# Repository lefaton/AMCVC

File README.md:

# AMCVC — Arduino MIDI to CV Converter

A MIDI-to-CV daughter board designed to drive the [x0x-heart](http://www.openmusiclabs.com/projects/x0x-heart/) — an open-source clone of the Roland TB-303 bass synthesizer engine. The board sits between a MIDI source and the x0x-heart, converting MIDI note and CC messages into analog control voltages (CV) and digital gate/control signals.

Built around a **Teensy++ 1.0** microcontroller and a **MCP4922 12-bit dual DAC** via SPI. The firmware is written as an Arduino sketch.

> **Status:** The firmware is working and was successfully tested on a prototype. The
> schematic and board netlist have been corrected (2026 revision) — the two changed nets
> (`~SHDN`, `~LDAC`) still need re-routing in Eagle plus a DRC pass before fabrication.

---

## Context — What Is the x0x-heart?

The [x0x-heart](http://www.openmusiclabs.com/projects/x0x-heart/) is an open hardware recreation of the Roland TB-303 synthesizer core. It exposes CV and gate inputs for pitch, filter cutoff, and a set of digital control lines (decay, accent, slide in, slide out) that replicate the 303's characteristic playing articulations.

The AMCVC board plugs into those inputs and translates MIDI messages into the signals the x0x-heart expects, making it possible to sequence and play the 303 engine from any standard MIDI controller or DAW.

---

## Hardware Overview

### Microcontroller — Teensy++ 1.0

The [Teensy++ 1.0](https://www.pjrc.com/teensy/) is a compact USB-capable AVR microcontroller board (AT90USB1286). It runs the Arduino-compatible MIDI library and handles SPI communication with the DAC. A reference pinout is included in `Documents/Teensy 1.0++ pinout.png`.

### DAC — MCP4922 (12-bit, dual-channel, SPI)

The [MCP4922](https://www.microchip.com/MCP4922) is a 12-bit dual-output DAC communicating over SPI. It provides two independent CV outputs:

| Channel | Purpose     | Constant         | Driven by         |
|---------|-------------|------------------|-------------------|
| A (0)   | VCO pitch   | `VCO_DAC_ID = 0` | MIDI note number  |
| B (1)   | VCF cutoff  | `VCF_DAC_ID = 1` | MIDI CC 74        |

SPI is configured MSB-first, SPI Mode 0. The 16-bit command word sent to the MCP4922 is:

```
Bit 15   : A/B   — channel select (0 = channel A / VCO, 1 = channel B / VCF)
Bit 14   : BUF   — input buffer (0 = unbuffered)
Bit 13   : /GA   — gain select (1 = 1× gain, 0–Vref)
Bit 12   : /SHDN — output enable (1 = active)
Bits 11–0: 12-bit DAC value
```

`WriteDAC(channel, value)` builds the word per channel: it ORs in `0x3000` (bits 13
and 12 → 1× gain, output active) and sets bit 15 from the channel argument, so both
the VCO (channel A) and VCF (channel B) outputs are addressable.

### MIDI Isolation — 6N138 Optocoupler

MIDI input is electrically isolated using a [6N138](Documents/Datasheets/6N138.pdf) high-speed optocoupler, following the standard MIDI electrical interface specification. This prevents ground loops between the MIDI source and the synth circuitry.

---

## Pin Assignments (Teensy++ 1.0)

| Pin | Direction | Function                     |
|-----|-----------|------------------------------|
| 2   | INPUT     | MIDI input (via 6N138)       |
| 4   | OUTPUT    | Decay control (x0x-heart)    |
| 5   | OUTPUT    | Front panel LED              |
| 6   | OUTPUT    | Board LED                    |
| 7   | OUTPUT    | Accent control (x0x-heart)   |
| 8   | OUTPUT    | Slide In control             |
| 9   | OUTPUT    | VCO Gate                     |
| 10  | OUTPUT    | SPI CS (MCP4922 chip select) |
| 11  | OUTPUT    | SPI LDAC (DAC latch)         |
| 12  | OUTPUT    | Slide Out control            |
| 13  | INPUT     | Square wave input (x0x)      |
| 14  | INPUT     | Saw wave input (x0x)         |
| 15  | OUTPUT    | Square wave output           |
| 16  | OUTPUT    | Saw wave output              |
| 17  | OUTPUT    | VCF Gate                     |

---

## MIDI Configuration

```cpp
const int MIDIChannel = 3;  // MIDI channel to listen on
```

The sketch listens on MIDI channel 3 only — `MIDI.begin(MIDIChannel)` filters out
all other channels at the library level. To change channel, edit this constant and
re-upload.

---

## MIDI Note to CV Conversion

### Pitch (VCO)

The firmware converts MIDI note numbers to a 12-bit DAC value using a linear mapping:

```cpp
const float VCO_CV_step     = 68.25;  // DAC counts per semitone
const int   MIDI_Min_Note   = 24;     // C1 (lowest accepted note)
const int   MIDI_Max_Note   = 84;     // C6 (highest accepted note)
const int   MIDI_Start_Offset = 24;   // note 24 maps to DAC value 0
const int   VCO_CV_Offset   = 0;      // global tuning offset in semitones
```

Conversion formula:

```
convertedVal = (note + VCO_CV_Offset - MIDI_Start_Offset) × VCO_CV_step
```

**Example values:**

| MIDI Note | Note Name     | DAC value | Approx. CV |
|-----------|---------------|-----------|------------|
| 24        | C1            | 0         | 0 V        |
| 36        | C2            | 819       | ~1 V       |
| 48        | C3            | 1638      | ~2 V       |
| 60        | C4 (middle C) | 2457      | ~3 V       |
| 72        | C5            | 3276      | ~4 V       |
| 84        | C6            | 4095      | ~5 V       |

The 60-semitone range (C1–C6) maps to 0–4095, giving **1V/octave** when the DAC reference voltage is 5V. Fine-tune `VCO_CV_step` if your VCO has a different V/oct scaling. The full lookup table is in `Documents/table_midi_cv.xlsx`.

### Gate

| MIDI event              | Gate pins      | Logic         |
|-------------------------|----------------|---------------|
| Note On (velocity > 0)  | pin 9 + pin 17 | LOW (active)  |
| Note Off / velocity = 0 | pin 9 + pin 17 | HIGH (off)    |

The x0x-heart gates are active-low. Both the VCO gate (pin 9) and VCF gate (pin 17)
are driven together.

### Note priority (monophonic note stack)

The firmware is monophonic but tracks held notes in a small stack (up to 8 notes):

- **Note On** pushes the note and plays it immediately (last-note priority).
- **Note Off** removes the note from the stack. Releasing a note that is *not* the
  one currently sounding does **not** cut the gate — it just leaves the stack.
- Releasing the sounding note falls back to the most recently held note still down;
  the gate only closes when no notes remain.

This makes legato/overlapping play behave the way a hardware mono synth does.

### VCF cutoff (CC 74)

MIDI **CC 74** (the standard "brightness"/cutoff controller) drives the VCF on DAC
channel B. Values 0–127 are mapped linearly to the full 12-bit range (0–4095).

---

## TB-303 Specific CC Messages

The x0x-heart exposes four articulation controls specific to the TB-303 playing style. The firmware maps MIDI CC messages to digital lines:

| CC  | Hex   | Function   | Effect when value > 100          |
|-----|-------|------------|----------------------------------|
| 99  | 0x63  | Decay      | Pin 4 LOW (decay enabled)        |
| 100 | 0x64  | Accent     | Pin 7 LOW (accent enabled)       |
| 101 | 0x65  | Slide In   | Pin 8 LOW (slide in enabled)     |
| 102 | 0x66  | Slide Out  | Pin 12 LOW (slide out enabled)   |

A CC value strictly above 100 (`triggerLimit = 0x64`) activates the control; 100 or
below deactivates it. CC 74 (cutoff) is the exception — it is a continuous value, not
a trigger (see [VCF cutoff](#vcf-cutoff-cc-74) above).

**Slide mutual exclusion:** Slide In and Slide Out are mutually exclusive — activating one automatically cancels the other, mirroring the 303's hardware behavior.

---

## Wave Pass-Through

The x0x-heart outputs both a **square wave** and a **sawtooth wave**. The AMCVC board reads these on pins 13/14 and re-outputs them on pins 15/16 every loop cycle, acting as a signal buffer:

```cpp
digitalWrite(sawWaveOut_Pin,    digitalRead(sawWaveIn_Pin));
digitalWrite(squareWaveOut_Pin, digitalRead(squareWaveIn_Pin));
```

---

## Repository Structure

```
sketch_MIDI_to_CV/
  sketch_MIDI_to_CV.ino       ← Arduino firmware (upload this to Teensy)

Documents/
  table_midi_cv.xlsx          ← Full MIDI note to CV conversion table
  Teensy 1.0++ pinout.png     ← Teensy++ 1.0 pin reference diagram
  x0x Heart - tb-303.fpd     ← Front panel design (Frontpanel Designer)
  x0xheartmanual.pdf          ← x0x-heart complete manual

  Eagle/
    *.sch   ← Circuit schematic (Eagle CAD) — use this as reference
    *.brd   ← PCB layout (Eagle CAD) ⚠️ 2 nets unrouted after netlist fix

  Datasheets/
    MCP4922.pdf               ← 12-bit dual DAC datasheet
    6N138.pdf                 ← MIDI optocoupler datasheet
```

> ⚠️ **PCB note:** The Eagle netlist bugs (`~SHDN` grounded, `~LDAC` floating) are fixed in
> both `.sch` and `.brd`. On the board these two nets are now **unrouted airwires** — open in
> Eagle, run ERC/forward-annotation, route `~SHDN` (→ +5V) and `~LDAC` (→ MCU pin 11), then DRC
> before sending to a fab.

---

## Setup

### Arduino Libraries Required

- **MIDI Library** — [FortySevenEffects/arduino_midi_library](https://github.com/FortySevenEffects/arduino_midi_library)
- **SPI** — built into the Arduino/Teensy core

### Upload Steps

1. Install [Teensyduino](https://www.pjrc.com/teensy/teensyduino.html)
2. Select board: **Teensy++ 1.0**
3. Set USB Type to **Serial** (for debug output)
4. Open `sketch_MIDI_to_CV/sketch_MIDI_to_CV.ino`
5. Upload

MIDI runs at 31250 baud on the hardware UART. Debug output runs at 57600 baud on USB Serial.

---

## Known Issues & Future Work

- **Two nets need routing** — after the 2026 netlist fixes, `~SHDN` and `~LDAC` are
  unrouted airwires on the board (see below); they must be routed in Eagle before a fab run
- **Monophonic only** — no chord support; the note stack gives last-note priority but a single voice
- **Firmware untested since revision** — the 2026 firmware changes (dual-channel DAC,
  VCF CC 74, note stack, channel filtering, non-blocking LED) have not yet been flashed
  and verified on hardware

### Fixed in the 2026 revision

**Schematic / PCB netlist** (corrected in both `.sch` and `.brd`, verified by netlist
re-parse — Eagle ERC/DRC still required):

- **DAC `~SHDN` no longer grounded** — pin 9 moved from `AGND` to `+5V`. It was tied to
  ground, which held both DAC outputs in permanent hardware shutdown (root cause of "no CV out")
- **DAC `~LDAC` now connected** — pin 8 wired to MCU pin 11; both were floating, so the
  latch line never transferred values to the outputs
- **VCF output labelled** — the `VOUTB` connector pad was renamed `UNUSED` → `VCF_CUTOFF`

> On the board, the two changed nets (`~SHDN`, `~LDAC`) are left as **airwires** — the old
> AGND copper at pad 9 was removed so nothing shorts. Open the `.brd` in Eagle, run
> ERC/forward-annotation, route the two airwires, then DRC.

**Firmware:**

- **VCF CV** — DAC channel B is now driven from MIDI CC 74
- **MIDI channel filtering** — `MIDI.begin(MIDIChannel)` replaces `MIDI_CHANNEL_OMNI`
- **Gate latency** — the LED blink is non-blocking, so Note On no longer delays the DAC write by 25 ms
- **Stuck-note edge cases** — a note stack prevents Note Off of an inactive note from cutting the gate

---

## License

GNU General Public License v2.0 — see [LICENSE](LICENSE).

If you use or build on this project, please mention [github.com/utopikprod](https://github.com/utopikprod/) as a reference.

---

## References

- [x0x-heart (Open Music Labs)](http://www.openmusiclabs.com/projects/x0x-heart/)
- [Teensy++ 1.0 (PJRC)](https://www.pjrc.com/teensy/)
- [MCP4922 datasheet](Documents/Datasheets/MCP4922.pdf)
- [6N138 optocoupler datasheet](Documents/Datasheets/6N138.pdf)
- [MIDI electrical specification](https://www.midi.org/specifications-old/item/midi-din-electrical-specification)

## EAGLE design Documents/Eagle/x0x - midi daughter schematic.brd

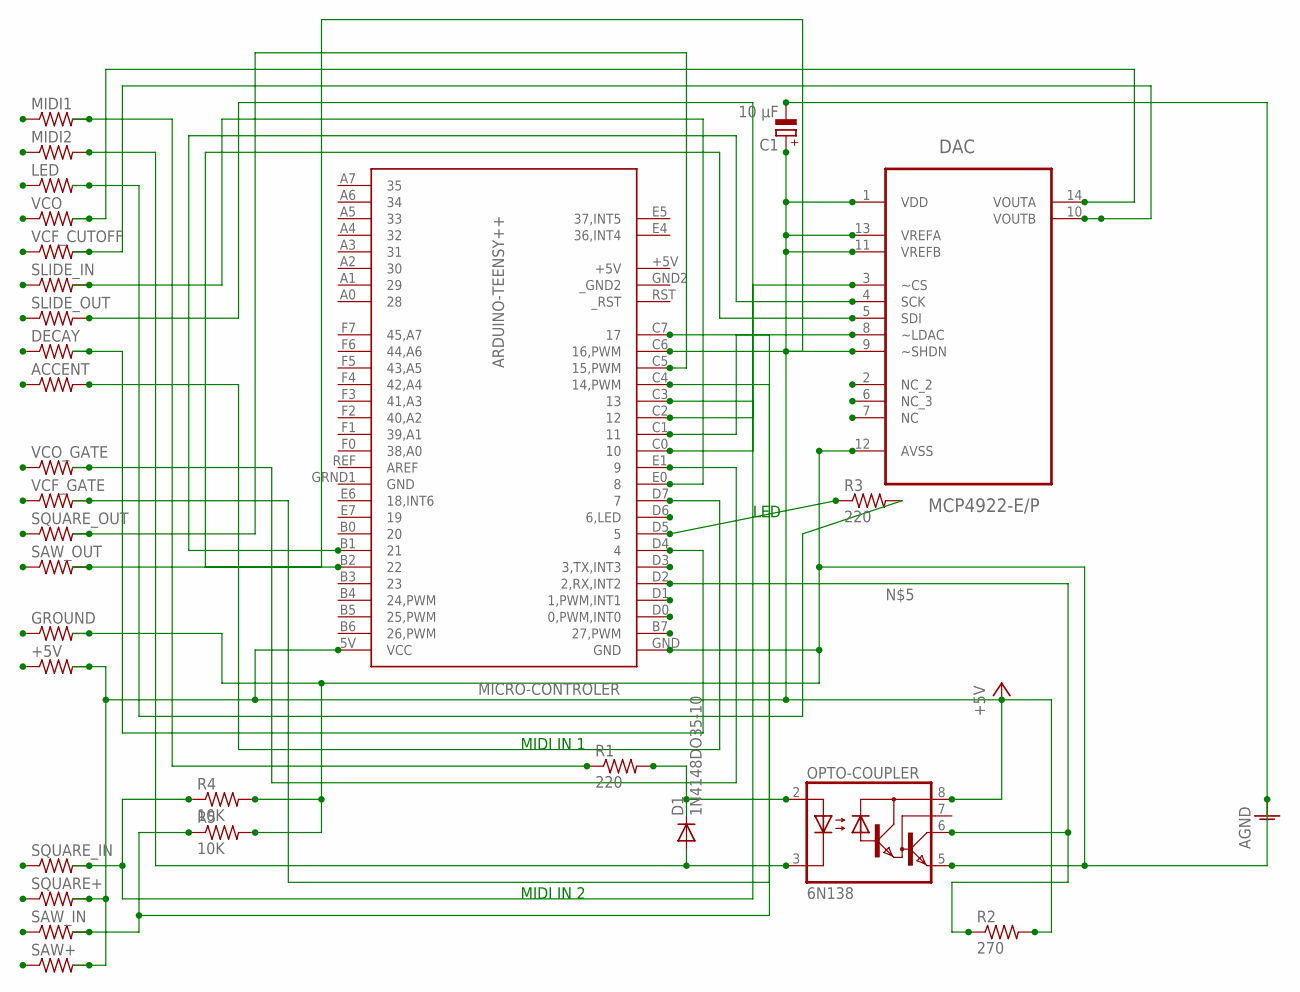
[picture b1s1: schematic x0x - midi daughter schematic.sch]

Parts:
+5V: R-US_0207/10; 0207/10
ACCENT: R-US_0207/10; 0207/10
C1: 10 µF; E1,8-4
D1: 1N4148DO35-10; DO35-10
DAC: MCP4922-E/P; DIP254P762X533-14
DECAY: R-US_0207/10; 0207/10
GROUND: R-US_0207/10; 0207/10
LED: R-US_0207/10; 0207/10
MICRO-CONTROLER: ARDUINO-TEENSY++; TEENSY++
MIDI1, MIDI2: R-US_0207/10; 0207/10
OPTO-COUPLER: 6N138; DIL08
R1, R3: 220; 0204/7
R2: 270; 0204/7
R4, R5: 10K; 0207/10
SAW+: R-US_0207/10; 0207/10
SAW_IN: R-US_0207/10; 0207/10
SAW_OUT: R-US_0207/10; 0207/10
SLIDE_IN: R-US_0207/10; 0207/10
SLIDE_OUT: R-US_0207/10; 0207/10
SQUARE+: R-US_0207/10; 0207/10
SQUARE_IN: R-US_0207/10; 0207/10
SQUARE_OUT: R-US_0207/10; 0207/10
VCF_CUTOFF: R-US_0207/10; 0207/10
VCF_GATE: R-US_0207/10; 0207/10
VCO: R-US_0207/10; 0207/10
VCO_GATE: R-US_0207/10; 0207/10

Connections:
+5V: +5V.2, C1.+, DAC.1 (VDD), DAC.9 (~SHDN), DAC.11 (VREFB), DAC.13 (VREFA), MICRO-CONTROLER.5V (VCC), MICRO-CONTROLER.+5V, OPTO-COUPLER.8 (VCC), R2.2, SAW+.2, SQUARE+.2
AGND: C1.-, DAC.12 (AVSS), GROUND.2, MICRO-CONTROLER.GND, OPTO-COUPLER.5 (GND), R4.2, R5.2
GND: MICRO-CONTROLER.GRND1 (GND)
unnamed: DAC.4 (SCK), MICRO-CONTROLER.B1 (21)
unnamed: DAC.5 (SDI), MICRO-CONTROLER.B2 (22)
unnamed: DAC.3 (~CS), MICRO-CONTROLER.C0 (10)
unnamed: D1.A, MIDI2.2, OPTO-COUPLER.3 (C)
unnamed: MICRO-CONTROLER.D2 (2,RX,INT2), OPTO-COUPLER.6 (VO), R2.1
unnamed: D1.C, OPTO-COUPLER.2 (A), R1.2
unnamed: MICRO-CONTROLER.D5 (5), R3.1
unnamed: MIDI1.2, R1.1
unnamed: MICRO-CONTROLER.C2 (12), SLIDE_OUT.2
unnamed: LED.2, R3.2
unnamed: DAC.14 (VOUTA), VCO.2
unnamed: DAC.10 (VOUTB), VCF_CUTOFF.2
unnamed: MICRO-CONTROLER.E0 (8), SLIDE_IN.2
unnamed: DECAY.2, MICRO-CONTROLER.D4 (4)
unnamed: ACCENT.2, MICRO-CONTROLER.D7 (7)
unnamed: MICRO-CONTROLER.E1 (9), VCO_GATE.2
unnamed: MICRO-CONTROLER.C7 (17), VCF_GATE.2
unnamed: MICRO-CONTROLER.C3 (13), R4.1, SQUARE_IN.2
unnamed: MICRO-CONTROLER.C4 (14,PWM), R5.1, SAW_IN.2
unnamed: MICRO-CONTROLER.C5 (15,PWM), SQUARE_OUT.2
unnamed: MICRO-CONTROLER.C6 (16,PWM), SAW_OUT.2
unnamed: DAC.8 (~LDAC), MICRO-CONTROLER.C1 (11)
_GND2: MICRO-CONTROLER.GND2 (_GND2)

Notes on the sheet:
LED
MIDI IN 1
MIDI IN 2

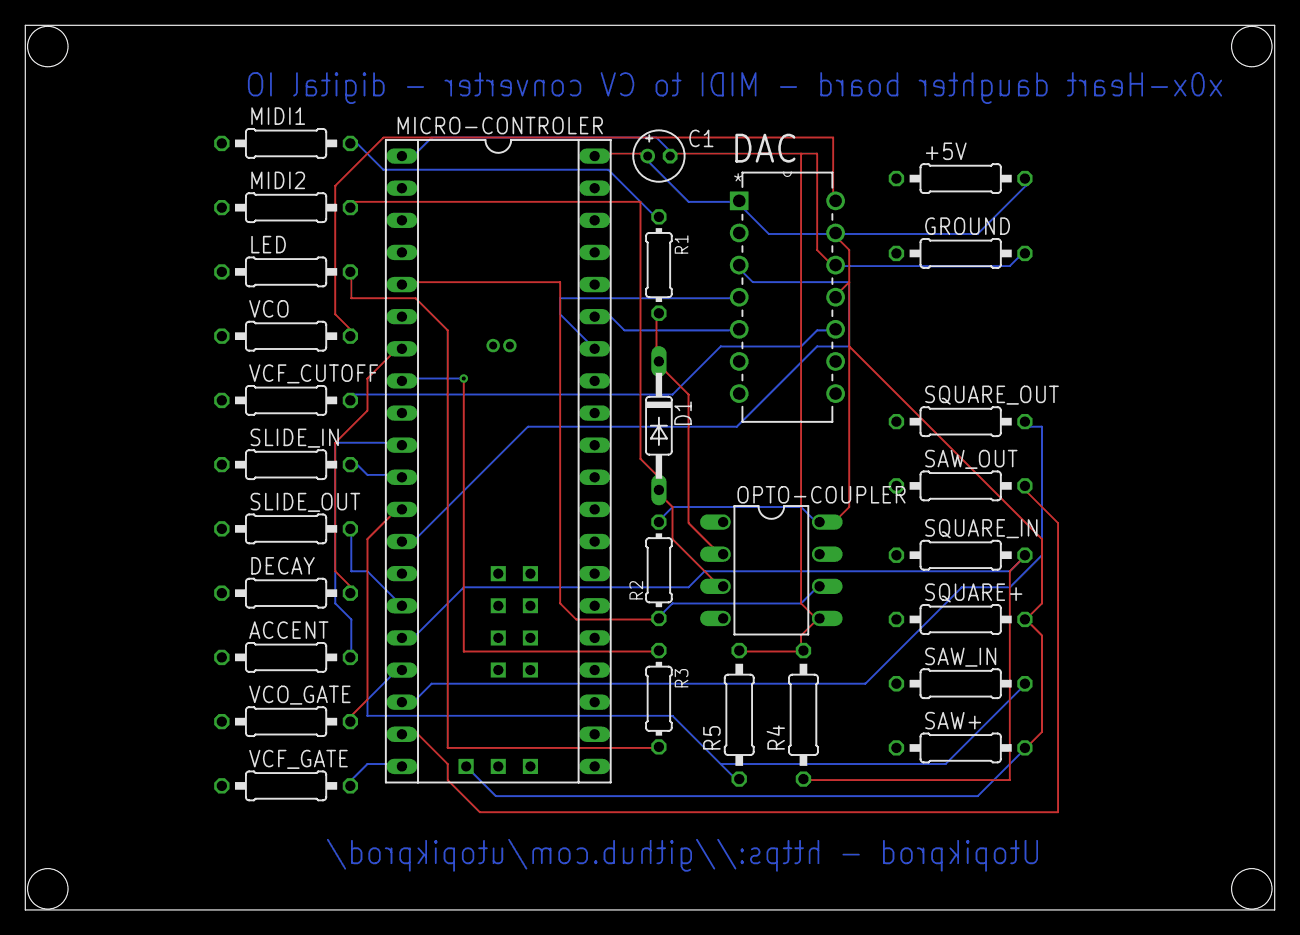
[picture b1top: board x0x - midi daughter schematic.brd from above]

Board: 2 copper layers, 98.8 x 69.9 mm, 29 parts (0 on the bottom side), 24 nets.

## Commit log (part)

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2014-03-04 Update README.md
    First words
2014-03-04 First Arduino handling since a while
    I tried some examples, I needed a reminder about MIDI norm for see how
    to implement the converter.
2014-03-07 Add Read/Write function
    Just add some logic in the code, nothing tested yet.
2014-03-07 Clean Read() function
    We just need to fill the buffer
2014-03-07 Code cleaning
    Use variable for buffer size
2014-03-10 Add DAC doc and code
    Continue with untested code. I will have to test many electronic things
    concerning timing issues before to continue.
2014-03-10 code cleaning
2014-03-11 Electronic schematics
    I did the electronic MIDI input with 6N138 optocoupler and started
    design around 74HC595 replacing the MIC810 for now
2014-03-11 Add 74HC595 code and some bytes conversions
    The code is still not tested, but almost finished for the first tests.
2014-03-11 Typo errors
2014-03-15 Replace serial by UART
2014-03-15 Fix buffer bug
2014-03-15 Use shiftOut() function add LSB pin for DAC
    shiftOut() function is a native arduino function for 74HC595 shift
    register, which does the same that I did for send bits one by one
2014-03-17 Add and move files
2014-03-17 Fix DAC output bug
2014-03-18 First EAGLE draft
2014-03-24 Refactor some functions
2014-03-26 Use MIDI lib for read input data
    Code refactor using the MIDI lib, because of some synchronous problems.
    Also removed buffering concept (useless).
2014-03-31 Remove 74HC595 from the schematic
    I removed the 74HC595, because it doesn't really help since I have
    enough pin on the board. But it worked and it was interresting to see
    how to use it. Also they are some bugfix.
2014-03-31 Add DAC Init
2014-04-01 Adapte MIDI range to tb-303 CV range
2014-04-14 Change DAC chip for a MCP4922
    Use a more popular and better documented DAC
2014-04-15 Fix last electronic issue
    Updated few documents
2014-04-15 Add pictures
2014-09-01 Add EAGLE components
2014-09-02 Add missing digital controls for x0x
    Added some code, pinout draw updated and few components added on EAGLE
2014-09-02 Handle correctly slide in / slide out
2014-09-15 Finalise PCB
    Finish PCB v 1.0
2014-10-12 Add board picture
2026-05-30 docs: rewrite README with full hardware details, pin table, MIDI-CV math and CC mapping
